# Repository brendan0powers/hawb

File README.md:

hawb
====

High altitude balloon project

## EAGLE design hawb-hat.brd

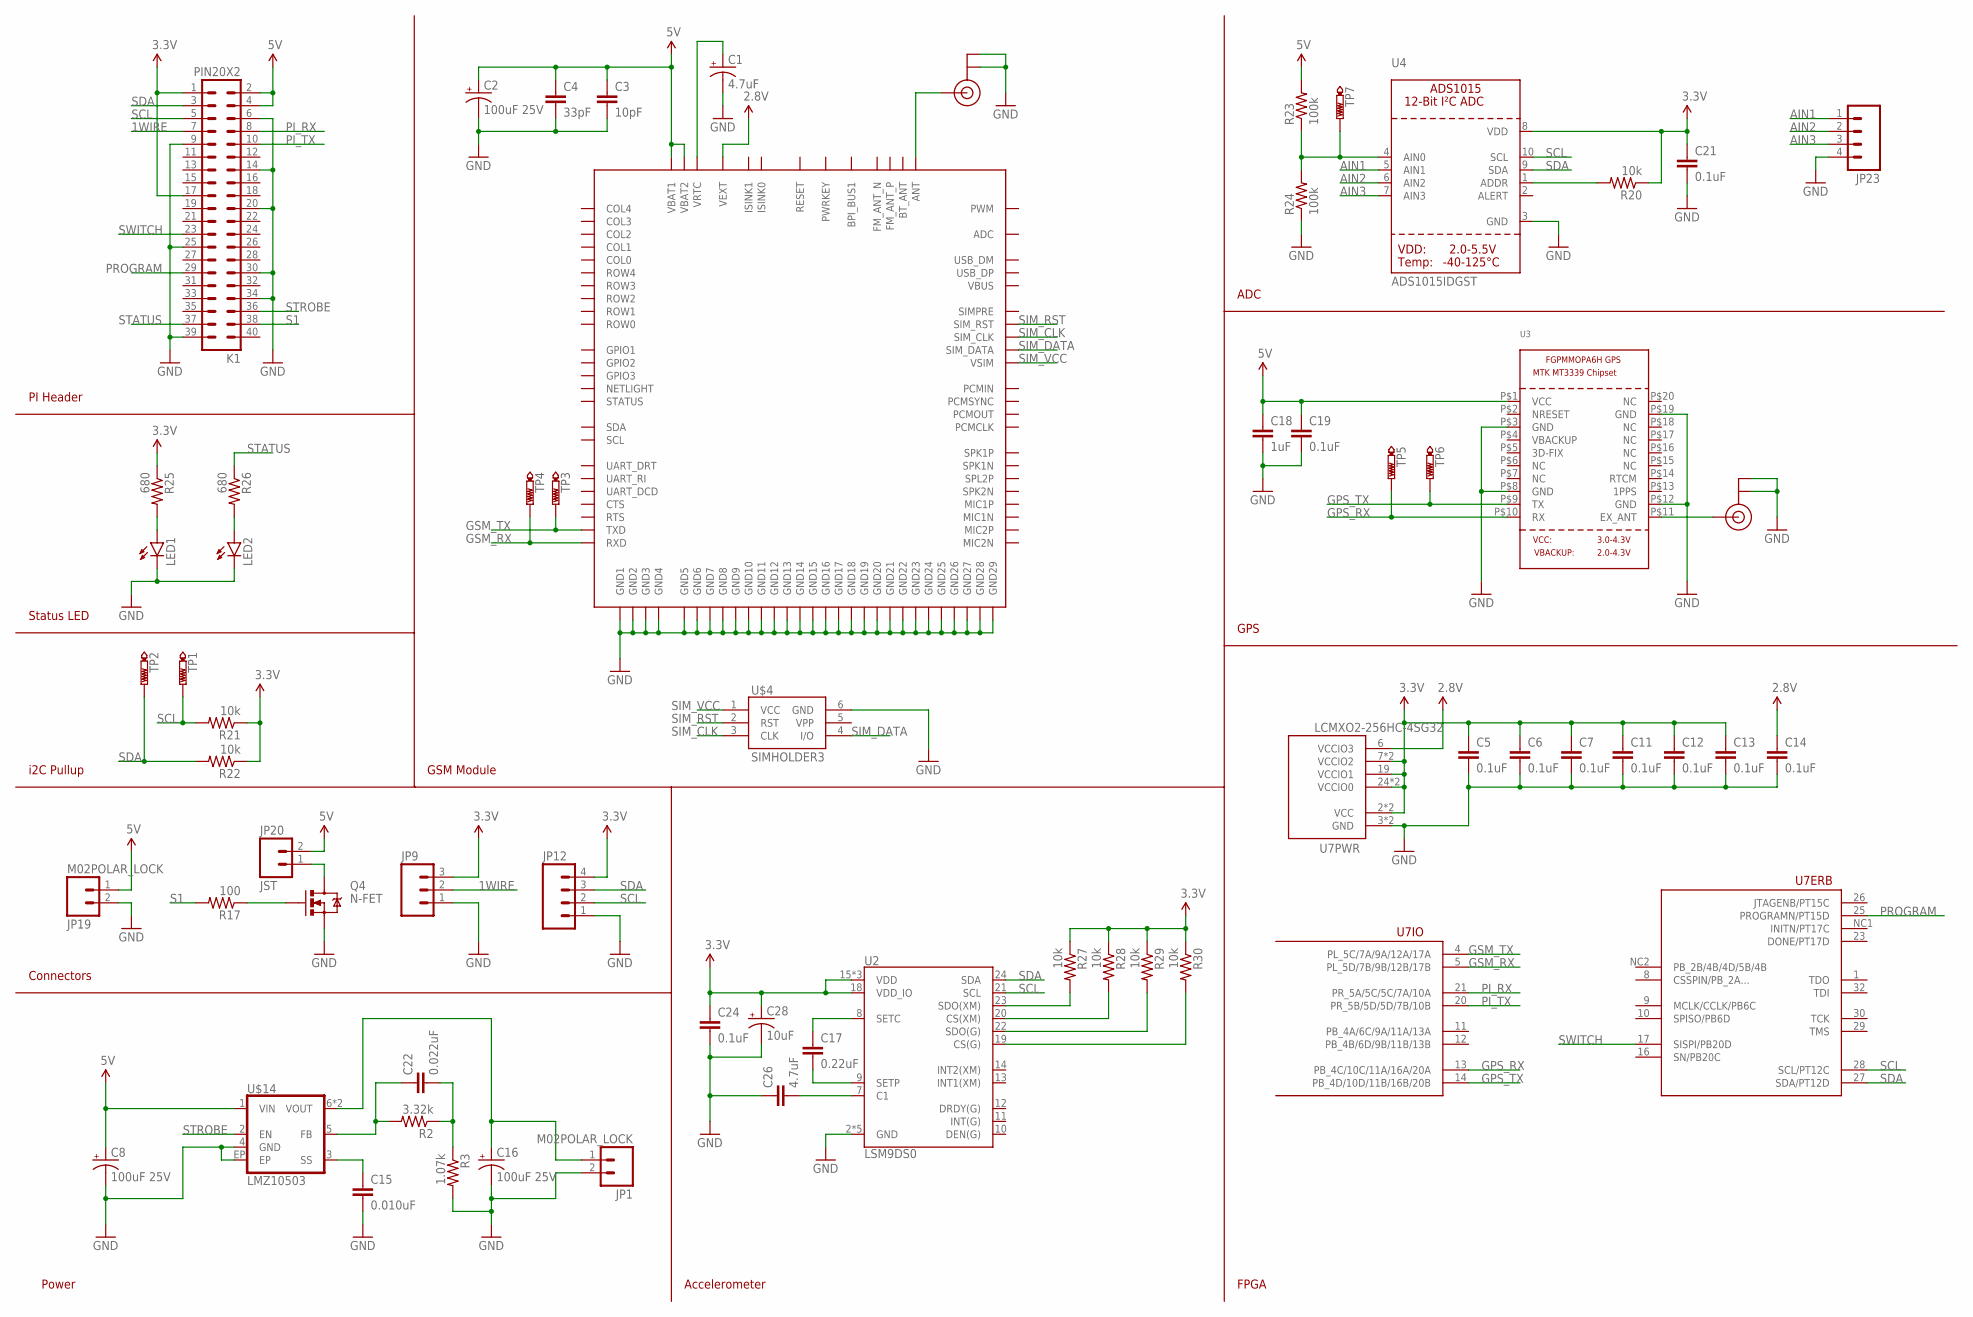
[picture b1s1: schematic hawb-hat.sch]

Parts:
C1: 4.7uF; EIA3216-KIT
C2, C8, C16: 100uF 25V; NIPPON_F80
C3: 10pF; C0603
C4: 33pF; C0603
C5, C6, C7, C11, C12, C13, C14, C19, C21: 0.1uF; C0603
C15: 0.010uF; C0603
C17: 0.22uF; 0603-CAP
C18: 1uF; C0603
C22: 0.022uF; C0603
C24: 0.1uF; 0603-CAP
C26: 4.7uF; 0603-CAP
C28: 10uF; EIA3216
JP1, JP19: M02POLAR_LOCK; MOLEX-1X2_LOCK
JP9: M03JST-PTH-VERT; JST-3-PTH-VERT
JP12, JP23: M04JST-PTH-VERT; JST-4-PTH-VERT
JP20: JST; JST-2-PTH-VERT
K1: PIN20X2; PIN_20X2
LED1, LED2: LED1206; LED-1206
Q4: N-FET; SOT23-3
R2: 3.32k; 0603-RES
R3: 1.07k; 0603-RES
R17: 100; 0603-RES
R20, R21, R22, R27, R28, R29, R30: 10k; 0603-RES
R23, R24: 100k; 0603-RES
R25, R26: 680; 0603-RES
TP1, TP2, TP3, TP4, TP5, TP6, TP7: PTR1PAD1-13; P1-13
U2: LSM9DS0; LGA-24
U3: GPS_FGPMMOPA6H; FGPMMOPA6H
U4: ADS1015IDGST; MSOP10
U7: LCMXO2-256HC-4SG32; QFN-32
U$1, U$2: U.FL
U$4: SIMHOLDER3
U$5: SIM800H; SIM800
U$14: LMZ10503; TO-PMOD-7

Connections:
1WIRE: JP9.2, K1.7
2.8V: C14.1, U7.6 (VCCIO3), U$5.P$18 (VEXT)
3.3V: C5.1, C6.1, C7.1, C11.1, C12.1, C13.1, C21.1, C24.1, C28.A (+), JP9.3, JP12.4, K1.1, K1.17, R20.1, R21.1, R22.1, R25.1, R27.1, R28.1, R29.1, R30.1, U2.15 (VDD), U2.16 (VDD), U2.17 (VDD), U2.18 (VDD_IO), U4.8 (VDD), U7.2 (VCC), U7.7 (VCCIO2), U7.15 (VCCIO2), U7.18 (VCC), U7.19 (VCCIO1), U7.24 (VCCIO0), U7.31 (VCCIO0)
5V: C2.+, C3.1, C4.1, C8.+, C18.1, C19.1, JP19.1, JP20.2, K1.2, K1.4, R23.2, U3.P$1 (VCC), U$5.P$1 (VBAT1), U$5.P$42 (VBAT2), U$14.1 (VIN)
AIN1: JP23.1, U4.5 (AIN1)
AIN2: JP23.2, U4.6 (AIN2)
AIN3: JP23.3, U4.7 (AIN3)
GND: C1.C (-), C2.-, C3.2, C4.2, C5.2, C6.2, C7.2, C8.-, C11.2, C12.2, C13.2, C14.2, C15.2, C16.-, C18.2, C19.2, C21.2, C24.2, C26.1, C28.C (-), JP1.2, JP9.1, JP12.1, JP19.2, JP23.4, K1.6, K1.9, K1.14, K1.20, K1.25, K1.30, K1.34, K1.39, LED1.C, LED2.C, Q4.2 (S), R3.2, R24.1, U2.2 (GND), U2.3 (GND), U2.4 (GND), U2.5 (GND), U2.6 (GND), U3.P$3 (GND), U3.P$8 (GND), U3.P$12 (GND), U3.P$19 (GND), U4.3 (GND), U7.3 (GND), U7.22 (GND), U$1.P$1 (GND), U$1.P$2 (GND), U$2.P$1 (GND), U$2.P$2 (GND), U$4.6 (GND), U$5.P$2 (GND1), U$5.P$6 (GND10), U$5.P$8 (GND11), U$5.P$35 (GND5), U$5.P$37 (GND6), U$5.P$38 (GND7), U$5.P$39 (GND8), U$5.P$41 (GND12), U$5.P$43 (GND2), U$5.P$44 (GND3), U$5.P$45 (GND4), U$5.P$58 (GND9), U$5.P$67 (GND13), U$5.P$71 (GND14), U$5.P$72 (GND15), U$5.P$73 (GND16), U$5.P$76 (GND17), U$5.P$77 (GND18), U$5.P$78 (GND19), U$5.P$79 (GND20), U$5.P$80 (GND21), U$5.P$81 (GND22), U$5.P$82 (GND23), U$5.P$83 (GND24), U$5.P$84 (GND25), U$5.P$85 (GND26), U$5.P$86 (GND27), U$5.P$87 (GND28), U$5.P$88 (GND29), U$14.4 (GND), U$14.EP
GPS_RX: TP5.TP, U3.P$10 (RX), U7.13 (PB_4C/10C/11A/16A/20A)
GPS_TX: TP6.TP, U3.P$9 (TX), U7.14 (PB_4D/10D/11B/16B/20B)
GSM_RX: TP4.TP, U7.5 (PL_5D/7B/9B/12B/17B), U$5.P$31 (RXD)
GSM_TX: TP3.TP, U7.4 (PL_5C/7A/9A/12A/17A), U$5.P$32 (TXD)
unnamed: C1.A (+), U$5.P$56 (VRTC)
unnamed: U$1.P$3 (SIGNAL), U$5.P$40 (ANT)
unnamed: LED1.A, R25.2
unnamed: C16.+, JP1.1, U$14.6 (VOUT), U$14.7 (VOUT)
unnamed: LED2.A, R26.2
unnamed: U3.P$11 (EX_ANT), U$2.P$3 (SIGNAL)
unnamed: R27.2, U2.23 (SDO(XM))
unnamed: R28.2, U2.20 (CS(XM))
unnamed: JP20.1, Q4.3 (D)
unnamed: Q4.1 (G), R17.1
unnamed: C15.1, U$14.3 (SS)
unnamed: C22.2, R2.1, R3.1
unnamed: C22.1, R2.2, U$14.5 (FB)
unnamed: R20.2, U4.1 (ADDR)
unnamed: R23.1, R24.2, TP7.TP, U4.4 (AIN0)
unnamed: C17.1, U2.8 (SETC)
unnamed: C17.2, U2.9 (SETP)
unnamed: R29.2, U2.22 (SDO(G))
unnamed: R30.2, U2.19 (CS(G))
unnamed: C26.2, U2.7 (C1)
PI_RX: K1.8, U7.21 (PR_5A/5C/5C/7A/10A)
PI_TX: K1.10, U7.20 (PR_5B/5D/5D/7B/10B)
PROGRAM: K1.29, U7.25 (PROGRAMN/PT15D)
S1: K1.38, R17.2
SCL: JP12.2, K1.5, R21.2, TP1.TP, U2.21 (SCL), U4.10 (SCL), U7.28 (SCL/PT12C)
SDA: JP12.3, K1.3, R22.2, TP2.TP, U2.24 (SDA), U4.9 (SDA), U7.27 (SDA/PT12D)
SIM_CLK: U$4.3 (CLK), U$5.P$55 (SIM_CLK)
SIM_DATA: U$4.4 (I/O), U$5.P$14 (SIM_DATA)
SIM_RST: U$4.2 (RST), U$5.P$15 (SIM_RST)
SIM_VCC: U$4.1 (VCC), U$5.P$16 (VSIM)
STATUS: K1.37, R26.1
STROBE: K1.36, U$14.2 (EN)
SWITCH: K1.23, U7.17 (SISPI/PB20D)

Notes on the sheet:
i2C Pullup
Status LED
PI Header
Power
FPGA
Accelerometer
Connectors
GSM Module
GPS
ADC

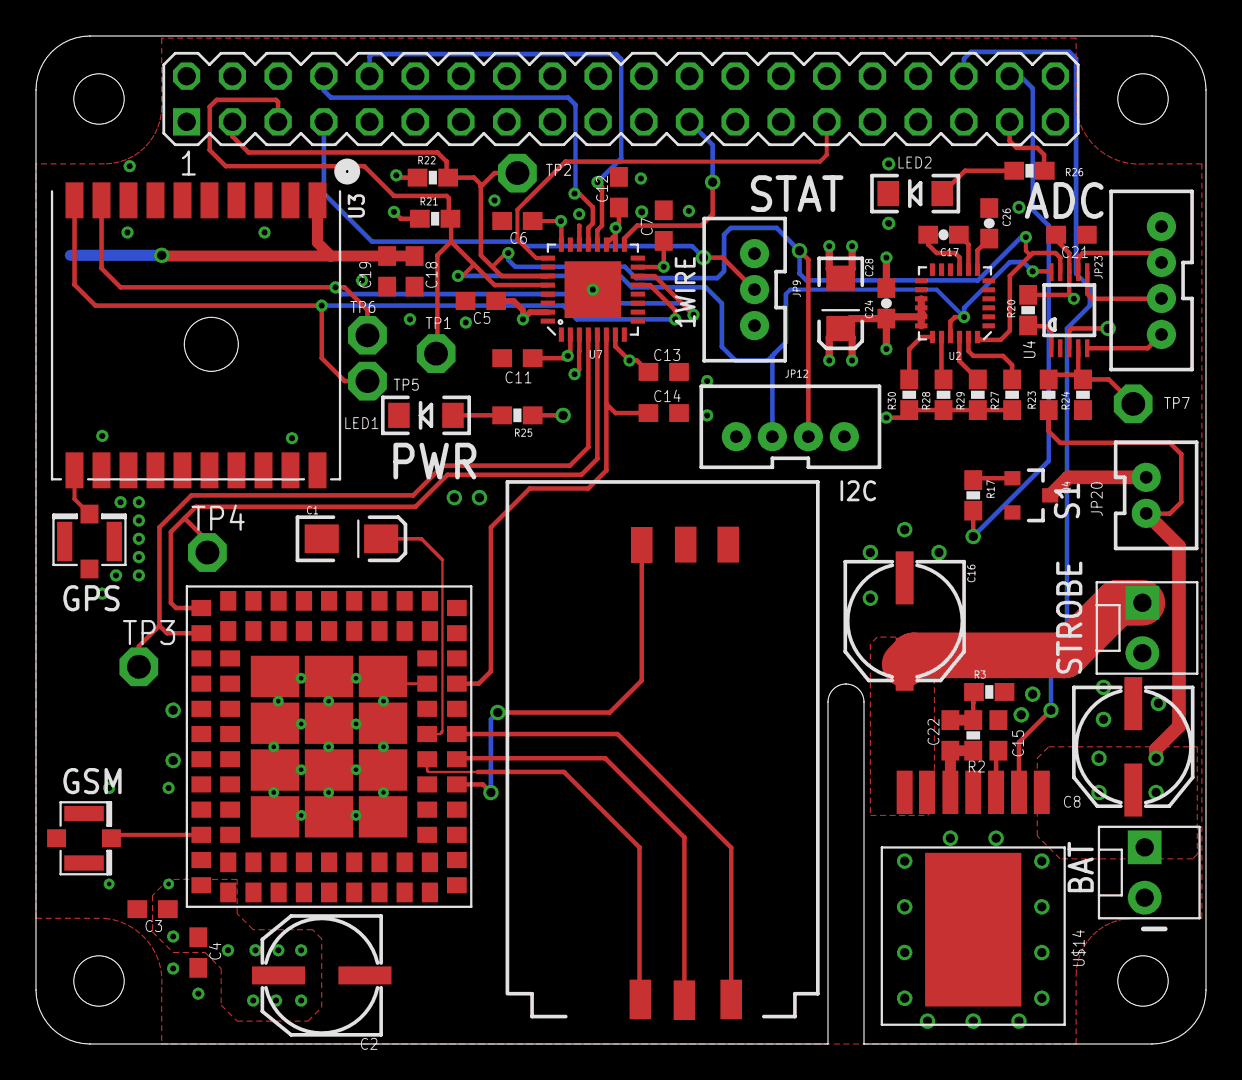
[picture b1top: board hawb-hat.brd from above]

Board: 4 copper layers, 65.0 x 56.0 mm, 62 parts (0 on the bottom side), 45 nets.

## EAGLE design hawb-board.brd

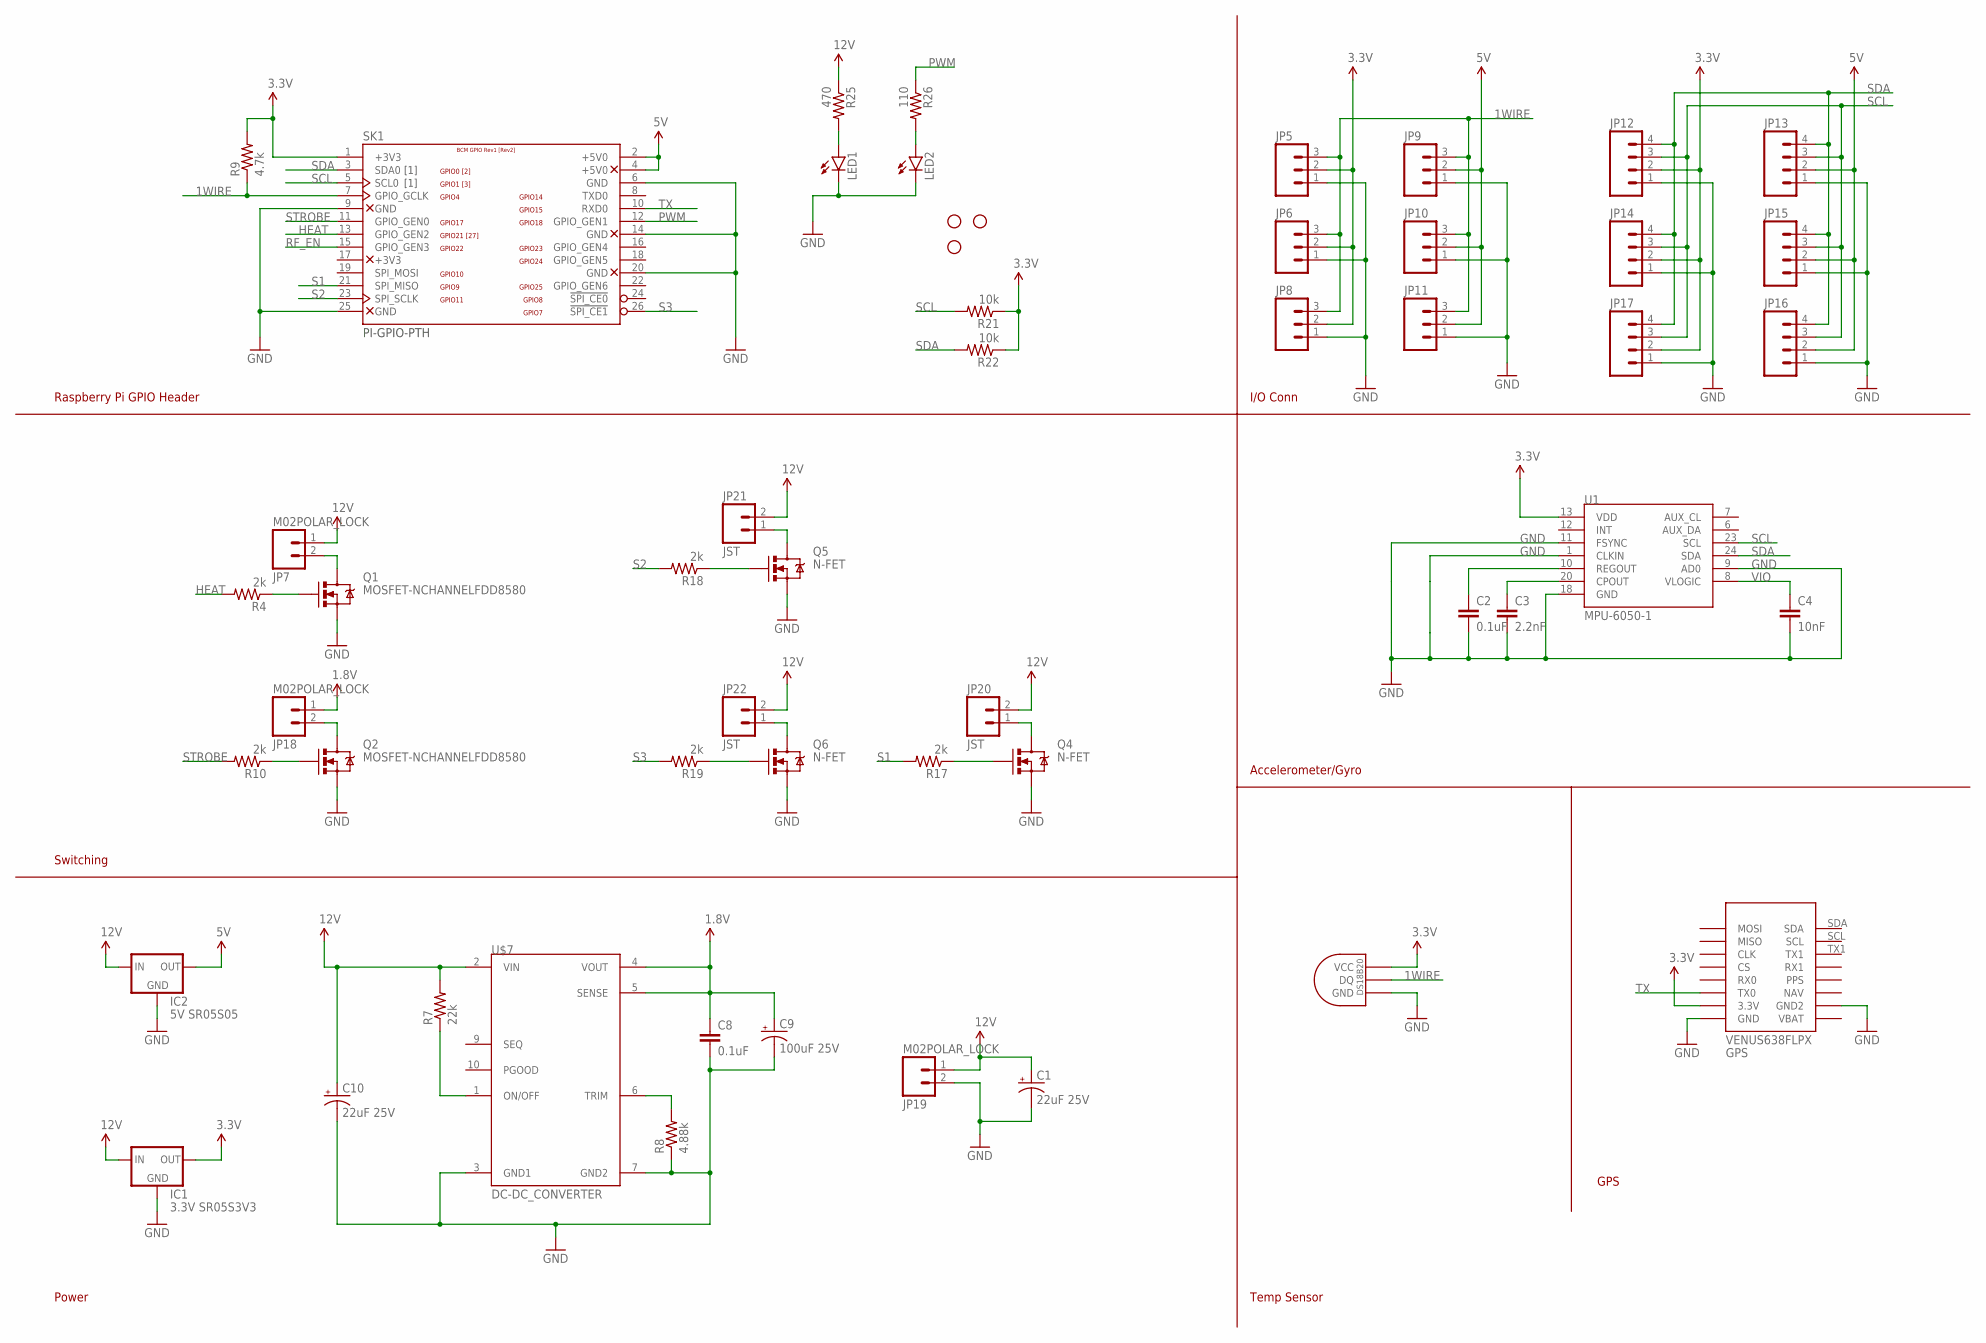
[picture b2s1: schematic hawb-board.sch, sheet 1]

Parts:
C1, C10: 22uF 25V; PANASONIC_C
C2: 0.1uF; 0402-CAP
C3: 2.2nF; 0402-CAP
C4: 10nF; 0402-CAP
C8: 0.1uF; C0603
C9: 100uF 25V; NIPPON_F80
GPS: VENUS638FLPX
IC1: 3.3V SR05S3V3; 78XXS
IC2: 5V SR05S05; 78XXS
JP1, JP2, JP4: STAND-OFF
JP5, JP6, JP8, JP9, JP10, JP11: M03JST-PTH-VERT; JST-3-PTH-VERT
JP7, JP18, JP19: M02POLAR_LOCK; MOLEX-1X2_LOCK
JP12, JP13, JP14, JP15, JP16, JP17: M04JST-PTH-VERT; JST-4-PTH-VERT
JP20, JP21, JP22: JST; JST-2-PTH-VERT
LED1, LED2: LED1206; LED-1206
Q1, Q2: MOSFET-NCHANNELFDD8580; DPAK
Q4, Q5, Q6: N-FET; SOT23-3
R4, R10, R17, R18, R19: 2k; 0603-RES
R7: 22k; 0603-RES
R8: 4.88k; 0603-RES
R9: 4.7k; 0603-RES
R21, R22: 10k; 0603-RES
R25: 470; 0603-RES
R26: 110; 0603-RES
SK1: PI-GPIO-PTH; GPIO-CONNECTOR
U1: MPU-6050-1; QFN-24-4MM2
U$4: DS1820SOIC; DS18B20_SOIC
U$7: DC-DC_CONVERTER

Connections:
1.8V: C8.1, C9.+, JP18.1, U$7.4 (VOUT), U$7.5 (SENSE)
1WIRE: JP5.3, JP6.3, JP8.3, JP9.3, JP10.3, JP11.3, R9.1, SK1.7 (GPIO_GCLK), U$4.DQ
3.3V: GPS.3.3V, IC1.OUT, JP5.2, JP6.2, JP8.2, JP12.2, JP14.2, JP17.2, R9.2, R21.1, R22.1, SK1.1 (+3V3), U1.13 (VDD), U$4.VCC; also elsewhere on the board
5V: IC2.OUT, JP9.2, JP10.2, JP11.2, JP13.2, JP15.2, JP16.2, SK1.2 (+5V0), SK1.4 (+5V0); also elsewhere on the board
GND: C1.-, C2.2, C3.2, C4.2, C8.2, C9.-, C10.-, GPS.GND, GPS.GND2, IC1.GND, IC2.GND, JP5.1, JP6.1, JP8.1, JP9.1, JP10.1, JP11.1, JP12.1, JP13.1, JP14.1, JP15.1, JP16.1, JP17.1, JP19.2, LED1.C, LED2.C, Q1.3 (S), Q2.3 (S), Q4.2 (S), Q5.2 (S), Q6.2 (S), R8.1, SK1.6 (GND), SK1.9 (GND), SK1.14 (GND), SK1.20 (GND), SK1.25 (GND), U1.1 (CLKIN), U1.9 (AD0), U1.11 (FSYNC), U1.18 (GND), U$4.GND, U$7.3 (GND1), U$7.7 (GND2); also elsewhere on the board
HEAT: R4.2, SK1.13 (GPIO_GEN2)
unnamed: JP7.2, Q1.4 (D)
unnamed: C3.1, U1.20 (CPOUT)
unnamed: Q1.1 (G), R4.1
unnamed: R8.2, U$7.6 (TRIM)
unnamed: R7.1, U$7.1 (ON/OFF)
unnamed: C2.1, U1.10 (REGOUT)
unnamed: JP18.2, Q2.4 (D)
unnamed: Q2.1 (G), R10.1
unnamed: JP20.1, Q4.3 (D)
unnamed: Q4.1 (G), R17.1
unnamed: JP21.1, Q5.3 (D)
unnamed: Q5.1 (G), R18.1
unnamed: JP22.1, Q6.3 (D)
unnamed: Q6.1 (G), R19.1
unnamed: LED1.A, R25.2
unnamed: LED2.A, R26.2
PWM: R26.1, SK1.12 (GPIO_GEN1)
RF_EN: SK1.15 (GPIO_GEN3); also elsewhere on the board
S1: R17.2, SK1.21 (SPI_MISO)
S2: R18.2, SK1.23 (SPI_SCLK)
S3: R19.2, SK1.26 (!SPI_CE1)
SCL: JP12.3, JP13.3, JP14.3, JP15.3, JP16.3, JP17.3, R21.2, SK1.5 (SCL0), U1.23 (SCL); also elsewhere on the board
SDA: JP12.4, JP13.4, JP14.4, JP15.4, JP16.4, JP17.4, R22.2, SK1.3 (SDA0), U1.24 (SDA); also elsewhere on the board
STROBE: R10.2, SK1.11 (GPIO_GEN0)
TX: GPS.TX0, SK1.10 (RXD0)
VCC: C1.+, C10.+, IC1.IN, IC2.IN, JP7.1, JP19.1, JP20.2, JP21.2, JP22.2, R7.2, R25.1, U$7.2 (VIN); also elsewhere on the board
VIO: C4.1, U1.8 (VLOGIC)

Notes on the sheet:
Raspberry Pi GPIO Header
Switching
Power
Temp Sensor
GPS
Accelerometer/Gyro
I/O Conn

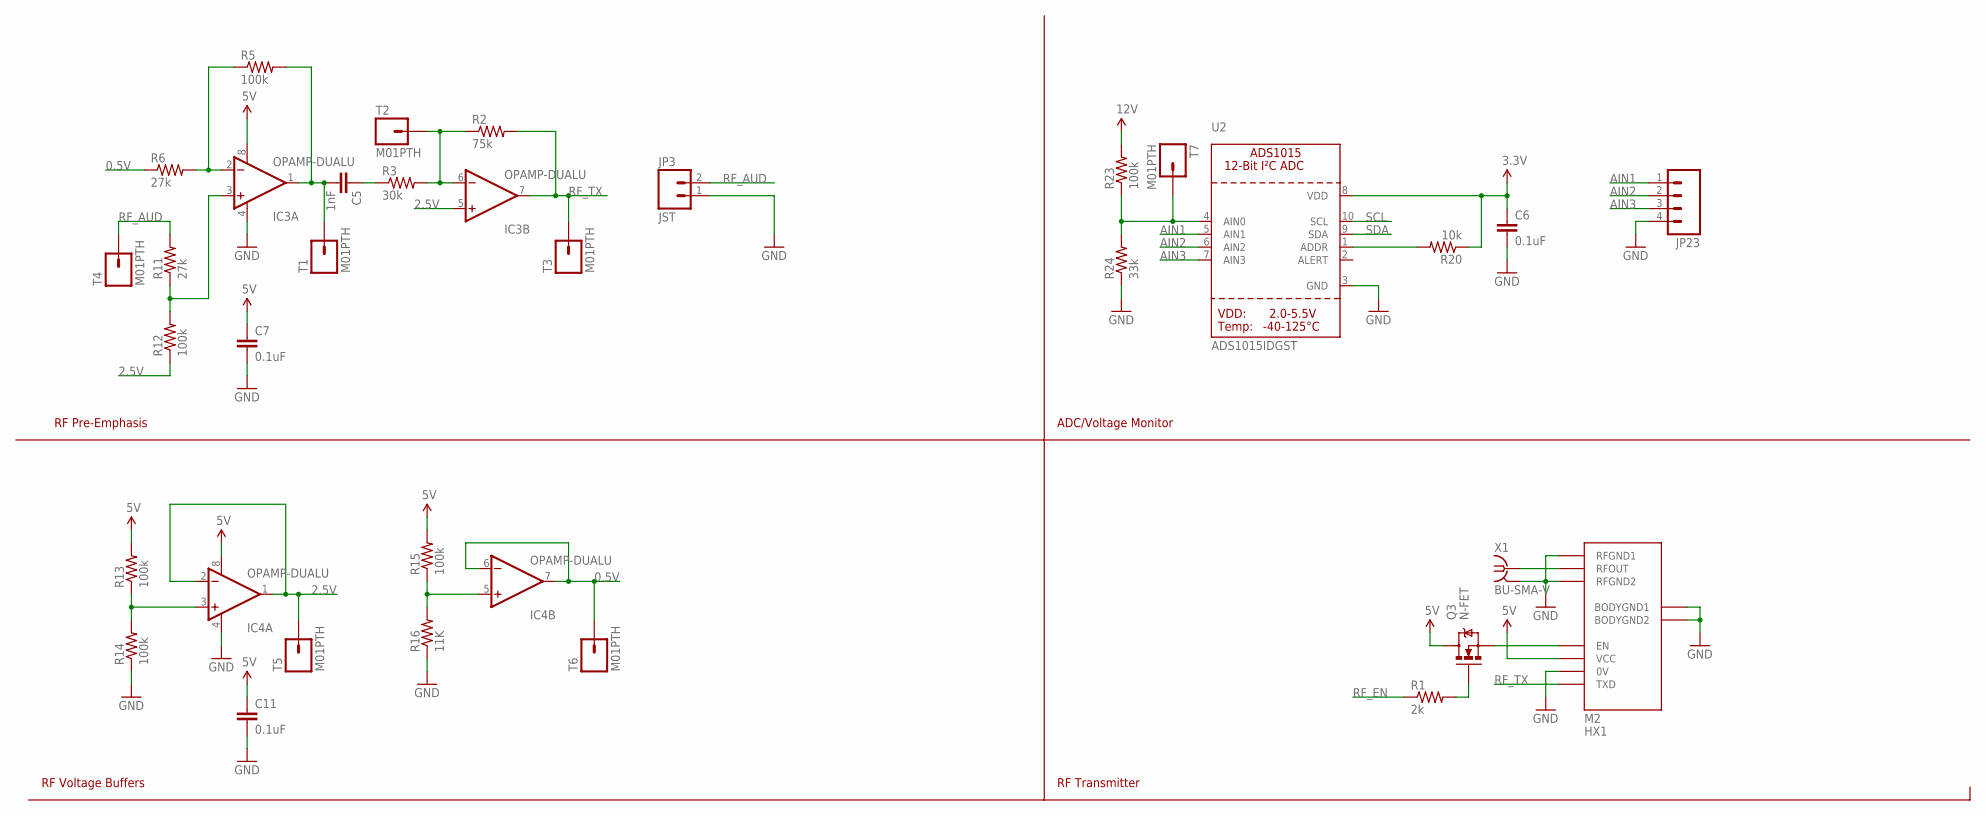
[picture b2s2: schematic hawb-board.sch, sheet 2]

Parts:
C5: 1nF; 0603-CAP
C6, C7, C11: 0.1uF; C0603
IC3, IC4: OPAMP-DUALU; SO08
JP3: JST; JST-2-PTH-VERT
JP23: M04JST-PTH-VERT; JST-4-PTH-VERT
M2: HX1
Q3: N-FET; SOT23-3
R1: 2k; 0603-RES
R2: 75k; 0603-RES
R3: 30k; 0603-RES
R5, R12, R13, R14, R15, R23: 100k; 0603-RES
R6, R11: 27k; 0603-RES
R16: 11K; 0603-RES
R20: 10k; 0603-RES
R24: 33k; 0603-RES
T1, T2, T3, T4, T5, T6, T7: M01PTH; 1X01
U2: ADS1015IDGST; MSOP10
X1: BU-SMA-V

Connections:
0.5V: IC4.6 (-IN), IC4.7 (OUT), R6.1, T6.1
2.5V: IC3.5 (+IN), IC4.1 (OUT), IC4.2 (-IN), R12.1, T5.1
3.3V: C6.1, R20.1, U2.8 (VDD); also elsewhere on the board
5V: C7.1, C11.1, IC3.8 (V+), IC4.8 (V+), M2.VCC, Q3.3 (D), R13.2, R15.2; also elsewhere on the board
AIN1: JP23.1, U2.5 (AIN1)
AIN2: JP23.2, U2.6 (AIN2)
AIN3: JP23.3, U2.7 (AIN3)
GND: C6.2, C7.2, C11.2, IC3.4 (V-), IC4.4 (V-), JP3.1, JP23.4, M2.0V, M2.BODYGND1, M2.BODYGND2, M2.RFGND1, M2.RFGND2, R14.1, R16.1, R24.1, U2.3 (GND), X1.2 (GND), X1.3 (GND), X1.4 (GND), X1.5 (GND); also elsewhere on the board
unnamed: M2.EN, Q3.2 (S)
unnamed: Q3.1 (G), R1.2
unnamed: M2.RFOUT, X1.1
unnamed: IC3.2 (-IN), R5.1, R6.2
unnamed: IC3.3 (+IN), R11.1, R12.2
unnamed: C5.1, R3.1
unnamed: C5.2, IC3.1 (OUT), R5.2, T1.1
unnamed: IC3.6 (-IN), R2.1, R3.2, T2.1
unnamed: IC4.3 (+IN), R13.1, R14.2
unnamed: IC4.5 (+IN), R15.1, R16.2
unnamed: R20.2, U2.1 (ADDR)
unnamed: R23.1, R24.2, T7.1, U2.4 (AIN0)
RF_AUD: JP3.2, R11.2, T4.1
RF_EN: R1.1; also elsewhere on the board
RF_TX: IC3.7 (OUT), M2.TXD, R2.2, T3.1
SCL: U2.10 (SCL); also elsewhere on the board
SDA: U2.9 (SDA); also elsewhere on the board
VCC: R23.2; also elsewhere on the board

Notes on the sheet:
RF Pre-Emphasis
RF Voltage Buffers
RF Transmitter
ADC/Voltage Monitor

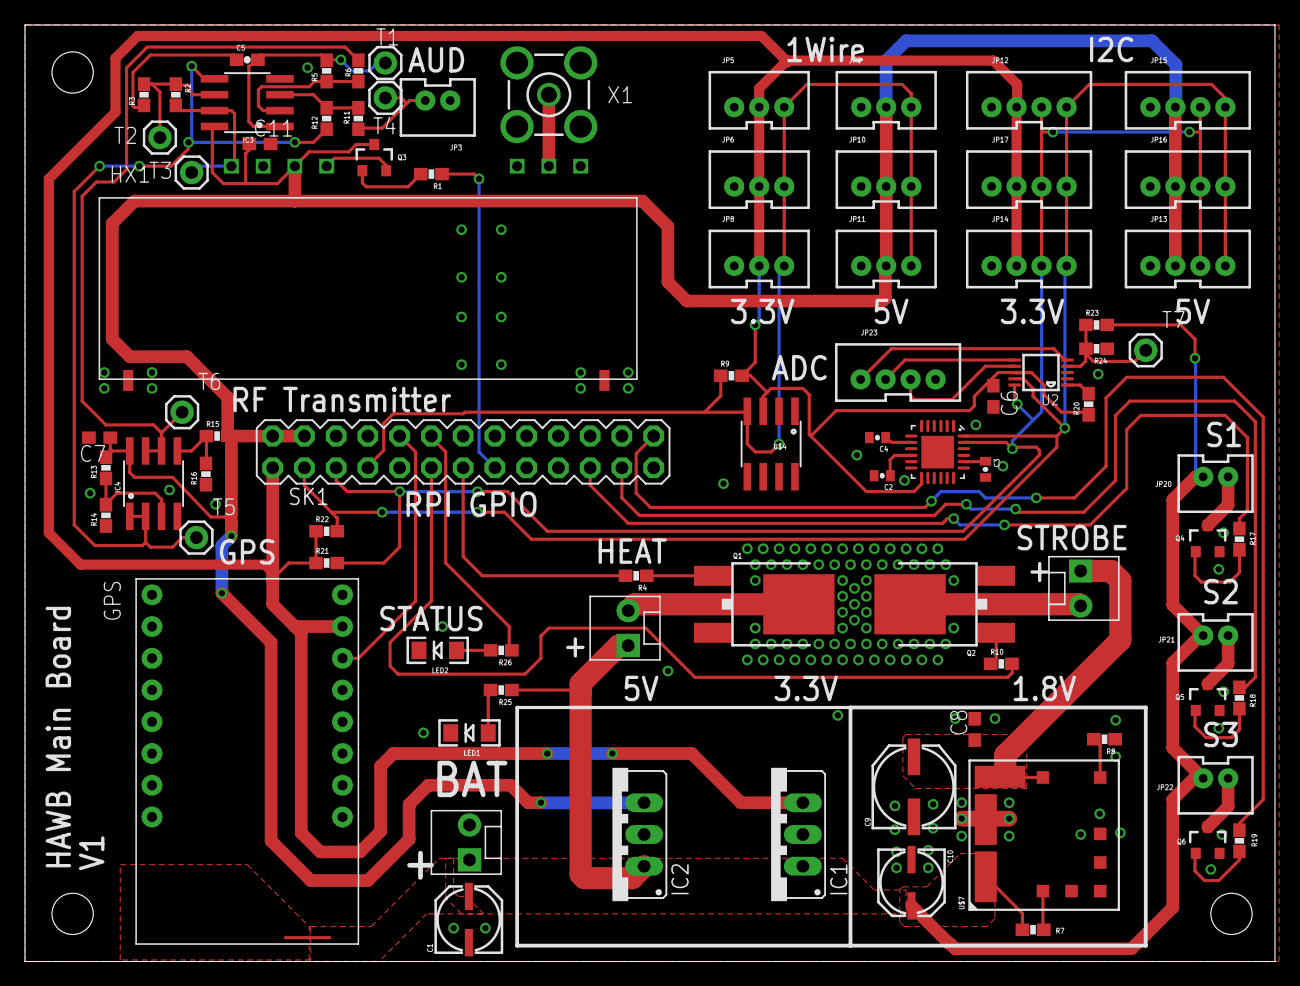
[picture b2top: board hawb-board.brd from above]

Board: 2 copper layers, 100.0 x 74.9 mm, 87 parts (0 on the bottom side), 52 nets.

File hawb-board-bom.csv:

Value	Parts	Device	Solder Type	Part Number	Qty	Source
	U2	ADC ADS1015	SMT/SMD	595-ADS1015IDGST	1	Mouser
0.1uF	C2, C6, C7, C8, C11	Cap 0603	SMT/SMD	81-GCM188R71H103KA7D	5	Mouser
10nF	C4	Cap 0603	SMT/SMD	81-GRM39X103K25	1	Mouser
1nF	C5	Cap 0603	SMT/SMD	81-GRM1885C1E102FA	1	Mouser
2.2nF	C3	Cap 0603	SMT/SMD	81-GCM188R71E223KA7D	1	Mouser
100uF 25V	C9	CAP POL	SMT/SMD	661-EMVY250ADA101MF8	1	Mouser
22uF 25V	C1, C10	CAP POL	SMT/SMD	667-EEE-1EA220WR	1	Mouser
	U$4	DS1820SOIC Temp Sensor	SMT/SMD	700-DS18S20Z	1	Mouser
	IC3, IC4	Dual Opamp	SMT/SMD	511-TS922IDT	2	Mouser
	LED1, LED2	LED1206	SMT/SMD	696-SML-1206GCTR1	2	Mouser
	U1	MPU-6050-1 Accel/Gyro	SMT/SMD	1428-1007-1-ND	1	Digi-Key
	Q1, Q2	N-MOSFET Dpack	SMT/SMD	512-FDD5353	2	Mouser
	Q3, Q4, Q5, Q6	N-MOSFET SOT-23-3	SMT/SMD	942-IRLML6344TRPBF	4	Mouser
110 Ohm	R26	Resistor 0603	SMT/SMD	71-CRCW0603-110-E3	1	Mouser
470 Ohm	R25	Resistor 0603	SMT/SMD	71-CRCW0603-470-E3	1	Mouser
100k	R5, R12, R13, R14, R15, R23	Resistor 0603	SMT/SMD	71-CRCW0603-100K-E3	6	Mouser
10k	R20, R21, R22	Resistor 0603	SMT/SMD	667-ERA-3AED103V	3	Mouser
11K	R16	Resistor 0603	SMT/SMD	71-CRCW0603-11K-E3	1	Mouser
22k	R7	Resistor 0603	SMT/SMD	71-CRCW0603-22K-E3	1	Mouser
27k	R6, R11	Resistor 0603	SMT/SMD	71-CRCW0603-27K-E3	2	Mouser
2k	R1, R4, R10, R17, R18, R19	Resistor 0603	SMT/SMD	71-CRCW0603-2.0K-E3	6	Mouser
30k	R3	Resistor 0603	SMT/SMD	71-CRCW0603-30K-E3	1	Mouser
33k	R24	Resistor 0603	SMT/SMD	71-CRCW0603-33K-E3	1	Mouser
4.88k	R8, R9	Resistor 0603	SMT/SMD	71-CRCW0603-4.87K-E3	2	Mouser
75k	R2	Resistor 0603	SMT/SMD	71-CRCW0603-75K-E3	1	Mouser
	IC1	Switching Regulator 3.3V	Through Hole	1470-2253-5-ND	1	Digi-Key
	IC2	Switching Regulator 5V 	Through Hole	1470-2249-5-ND	1	Digi-Key
	SK1	Header 26pin	Through Hole	517-929836-01-13	1	Mouser
	M2	HX1 Radio	Through Hole	HX1	1	Radiometrix
	JP3, JP20, JP21, JP22	JST Vertical 2Pin	Through Hole	455-1704-ND	4	Digi-Key
	JP5, JP6, JP8, JP9, JP10, JP11	JST Vertical 3Pin	Through Hole	455-1705-ND	6	Digi-Key
	JP12, JP13, JP14, JP15, JP16, JP17, JP23	JST Vertical 4Pin	Through Hole	455-1706-ND	7	Digi-Key
	JP7, JP18, JP19	Molex Vert 2Pin	Through Hole	538-22-23-2021	3	Mouser
	X1	SMA Connector	Through Hole	678-961A514	1	Mouser
	U$7	Switching Regulator 1.8V 	SMT/SMD	894-APXS003A0X4-SRZ	1	Mouser
						
					75	
Total

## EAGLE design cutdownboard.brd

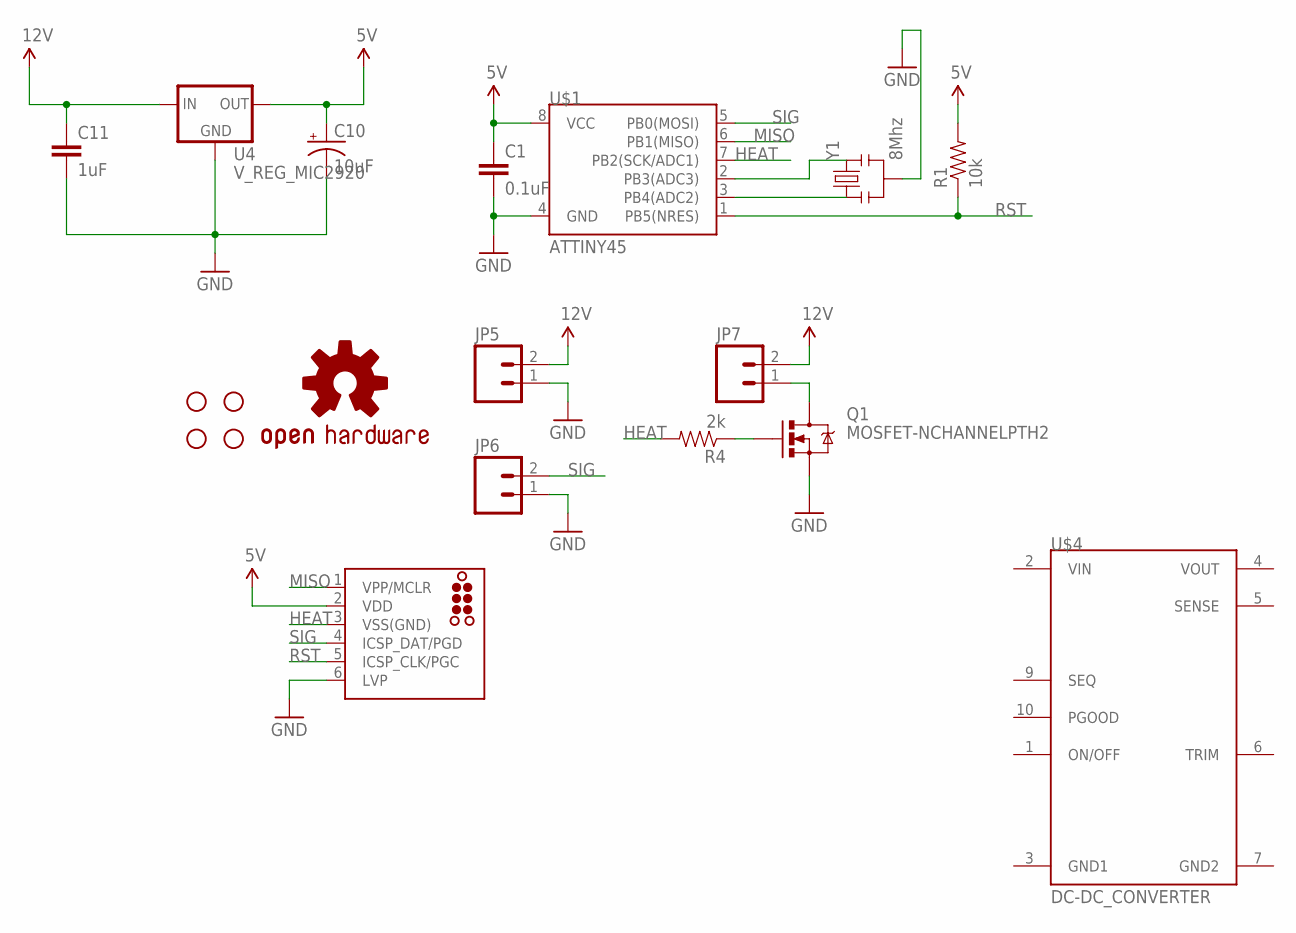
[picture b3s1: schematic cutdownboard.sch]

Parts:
C1: 0.1uF; C0603
C10: 10uF; EIA3216
C11: 1uF; C0603
J1: TC2030-MCP
JP1, JP2, JP3, JP4: STAND-OFF
JP5, JP6, JP7: M02JST-PTH-2; JST-2-PTH
Q1: MOSFET-NCHANNELPTH2; TO220V
R1: 10k; 0603-RES
R4: 2k; 0603-RES
U4: V_REG_MIC2920; SOT223
U$1: ATTINY45; SO08-EIAJ
U$4: DC-DC_CONVERTER
U$5: OSHW-LOGOS; OSHW-LOGO-S
Y1: 8Mhz; RESONATOR-SMD

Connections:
5V: C1.1, C10.A (+), J1.2 (VDD), R1.2, U4.3 (OUT), U$1.8 (VCC)
GND: C1.2, C10.C (-), C11.2, J1.6 (LVP), JP5.1, JP6.1, Q1.3 (S), U4.2 (GND), U$1.4 (GND), Y1.2
HEAT: J1.3 (VSS(GND)), R4.2, U$1.7 (PB2(SCK/ADC1))
MISO: J1.1 (VPP/MCLR), U$1.6 (PB1(MISO))
unnamed: U$1.3 (PB4(ADC2)), Y1.1
unnamed: U$1.2 (PB3(ADC3)), Y1.3
unnamed: JP7.1, Q1.2 (D)
unnamed: Q1.1 (G), R4.1
RST: J1.5 (ICSP_CLK/PGC), R1.1, U$1.1 (PB5(NRES))
SIG: J1.4 (ICSP_DAT/PGD), JP6.2, U$1.5 (PB0(MOSI))
VCC: C11.1, JP5.2, JP7.2, U4.1 (IN)

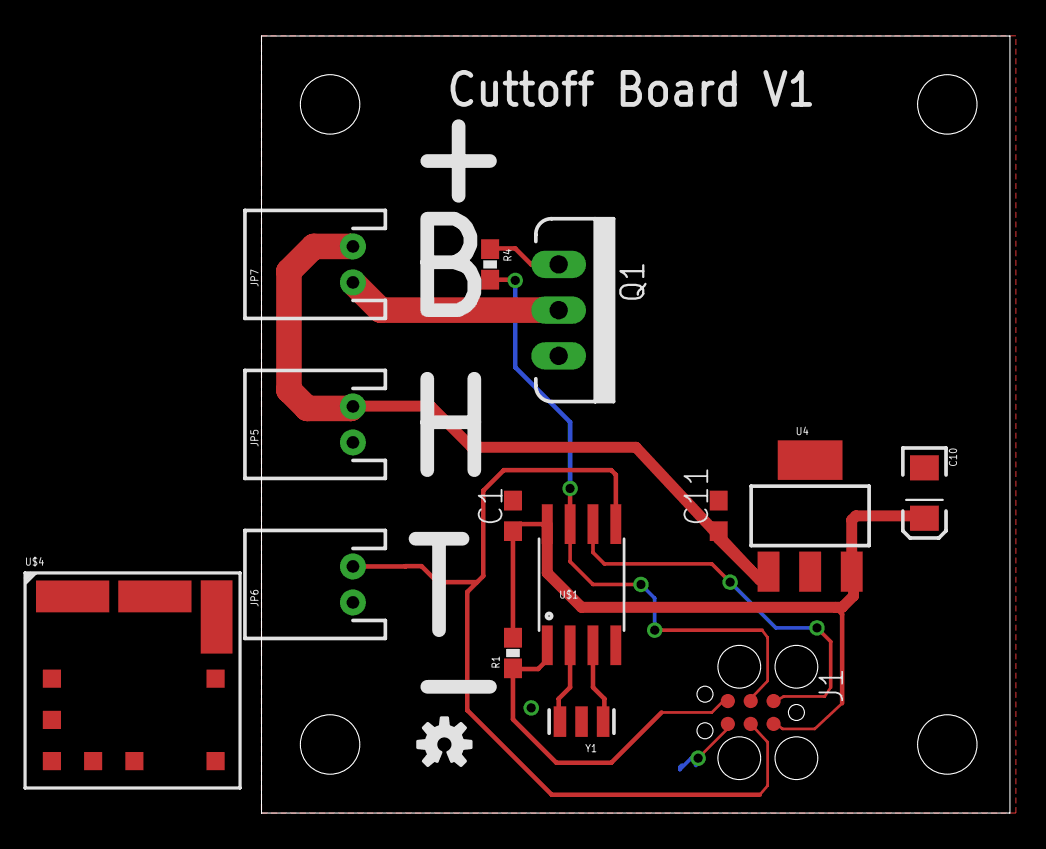
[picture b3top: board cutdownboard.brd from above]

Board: 2 copper layers, 41.6 x 43.2 mm, 19 parts (0 on the bottom side), 11 nets.

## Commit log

2014-05-17 Added Eagle Files
2014-05-17 Added some decoupling caps, bom
2014-05-18 Updated board, BOM
2015-02-23 First version of the raspberry pi hat board

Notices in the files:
parts and their libraries:
sparkfun: Licensing: CC v3.0 Share-Alike You are welcome to use this library for commercial purposes.
tag-connect: ©2009 ROFA.cz - modified and updated by Robert Darlington ‹rdarlington@gmail.com›
